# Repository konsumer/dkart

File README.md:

# dkart

An open-hardware and software Gameboy flash-cart and hardware peripheral framework that uses off-the-shelf hardware. The goal is to be ultra-cheap and simple.

## quickstart

If you just want to get started, go to [releases](https://github.com/konsumer/dkart/releases) and grab `dkart.gb`, and put it on a FAT32-formatted SDCard. Solder together the hardware, plug it in, and startup your gameboy.

## Hardware

It's meant to be very cheap & easy to put together. I made a PCB, and you can just solder in a [cheap ESP32 board](https://www.banggood.com/Geekcreit-ESP32-WiFibluetooth-Development-Board-Ultra-Low-Power-Consumption-Dual-Cores-Unsoldered-p-1214159.html) and the [SDCard shield](https://www.banggood.com/SD-Card-Module-Slot-Socket-Reader-Mp3-player-p-74105.html), and it should work.

Originally, I designed this as a custom circuit with really low-resource chips, but realized it was much easier and cheaper to just use more modern ready-made stuff.

Eventually I'd like to add an i2c bus that can be triggered/read from gameboy, so users can easily mess with hardware peripherals.

I am still working on the PCB & schematic. You can open hardware/Dkart.json at [easyeda](https://easyeda.com/).

### under consideration

Here are some other ideas I am looking at:

* [STM32F401](https://www.banggood.com/STM32F401-Development-Board-STM32F401CCU6-STM32F4-Learning-Board-p-1568897.html)
* [This board](https://www.banggood.com/LILYGO-TTGO-T2-ESP32-0_95-OLED-SD-Card-WiFi-bluetooth-Module-Development-Board-p-1270477.html) has a SDCard and OLED screen (and wifi/bluetooth)
* [cheap atmega2560 board](https://robotdyn.com/mega-2560-pro-mini-atmega2560-16au.html), works with arduino & has more IO/RAM/CPU, but still not big enough to hold every ROM
* [fast flash mem](https://www.sparkfun.com/products/15809) - I could load the rom & ram into flash temporarily on a lower-end microcontroller, then feed the data to the GB.
* [something like this](https://www.banggood.com/GY-Openlog-Cleanflight-Naze32-F3-Blackbox-Flash-Recorder-Module-p-1309673.html) has a lot of storage (32GB) but might not be fast enough
* [ready-made cart PCB](https://store.kitsch-bent.com/product/kk_gb_brkout) - with a little simple soldering and a big flash chip, I could probly get it all to fit inside a cartridge
* [something like this](http://ww1.microchip.com/downloads/en/DeviceDoc/20005023B.pdf) could be hooked up directly to GB pins, with maybe a little simple mode-management from a micro
* [sdfat](https://github.com/greiman/SdFat-beta) can do 3965.11 KB/Sec transfer in dedicated SPI with a slow cad, which should be fast enough
* [better SDCards](https://www.cameramemoryspeed.com/sd-memory-card-faq/fastest-memory-card/) can go much faster, so make sure to check SD speed (SDFst has a `bench` sketch)
* 3d print longer cart to hold more electronics if needed. [here](https://www.thingiverse.com/thing:2882206) are some nice variations. [Here](https://www.thingiverse.com/thing:3101147) is a nice modular design (opnscad - chnage logo, etc)
* I have a [ATxmega128A1 breakout](https://www.sparkfun.com/products/retired/9546) laying around, but it's discontinued at sparkfun. It has 78 IO and 32 MIPS! It only has 128kB of flash memory & 8 kB SRAM, but could be used easily with other things, possibly SD alone is fast enough.
* look at [this ESP32 cart](https://hackaday.io/project/20769-wifi-game-boy-cartridge). They have a lot of the same ideas.

## Firmware

The firmware runs on the device to emulate ROM/RAM reading/writing data to a microSD card formatted FAT16/FAT32/ExFat. The firmware is meant to be compiled in Arduino IDE. If you open serial-monitor when it's running, you'll see some debugging output. On Arch Linux, I had to use `arduino-PR-beta1.9-BUILD-117` for serial-monitor to work, due to some java error.

Files should all be in the root of the SDCard. The fRAM-size is 128K so you may hit limits if you have a ton of ROM files on the SD (limit should be around 8,737.) The file-list uses ROM-header-title, so if you have a bunch of the same ROM file-named differently, it will work, but in the ROM-list they will all have the same name. You can use this trick to have different copies of the same ROM with separate RAM files (like 1-per-song for nanoloop, for example.)

## Software

A menu runs on the Gameboy to choose the current ROM/RAM. When a ROM is chosen, the gameboy reboots using that ROM/RAM.

To compile, you need nodejs installed

```sh
cd software
npm i
npm run build
```

in the software directory. 

You can read more about it in [software](./software/README.md).

## TODO

* Actually Implement MBC1
* Get SD-loading working (on boot load into RAM from SD while playing logo)
* Get menu working (get list of ROMs from firmware, on menu selection, set mem, load on reboot & clear mem)
* Implement MBC5
* Replace Nintendo logo with mine
* add extra IO-functionality, reading/writing to a specific memory location to turn on "I/O mode" and be able to interface with other peripherals
* Add support for sub-directories
* Create a modern cross-platform GBDK-focused full dev-env (use wine & docker to run stuff like GBTD.) Alternately, write some web-based tools around GBDK.js to allow sprite/map/sound editing.

## License

* Hardware is licensed 
* Firmware & Software is licensed 

## Thanks

* Lots of hardware/firmware ideas from [here](https://dhole.github.io/post/gameboy_cartridge_emu_1/)
* Ideas for menu ROM programming from [gbdk_playground](https://github.com/mrombout/gbdk_playground), [gbdk-salvage](https://github.com/gbdk-salvage/grooves-game-boy-programming), & [GBSoundDemo](https://github.com/Zal0/GBSoundDemo)

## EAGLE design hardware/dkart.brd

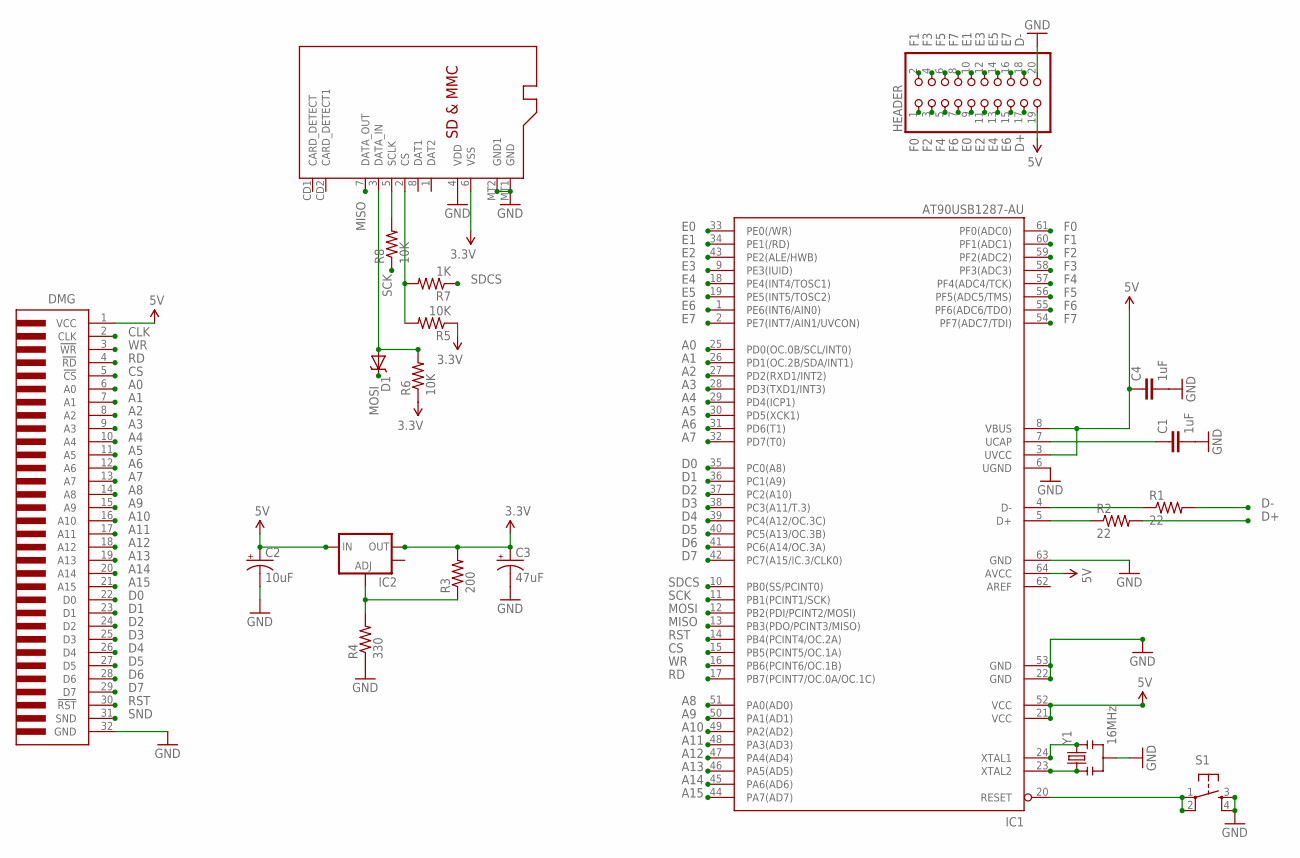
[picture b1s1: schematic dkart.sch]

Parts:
C1, C4: 1uF; 0805
C2: 10uF; EIA3528-KIT
C3: 47uF; EIA3528-KIT
D1: B340A; SMA-DIODE
DMG: GBCART-FULL; GBCART
HEADER: PINHD-2X10/90; 2X10/90
IC1: AT90USB1287-AU; TQFP64
IC2: V_REG_LM1117SOT223; SOT223
R1, R2: 22; 0805
R3: 200; 0805
R4: 330; 0805
R5, R6, R8: 10K; 0805
R7: 1K; 0805
S1: TAC_SWITCHSMD; TACTILE_SWITCH_SMD
SD: MICROSD
Y1: 16MHz; RESONATOR-SMD

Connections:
3.3V: C3.A (+), IC2.2 (OUT), R3.2, R5.1, R6.1, SD.6 (VSS)
5V: C2.A (+), C4.1, DMG.1 (VCC), HEADER.19, IC1.3 (UVCC), IC1.8 (VBUS), IC1.21 (VCC), IC1.52 (VCC), IC1.64 (AVCC), IC2.3 (IN)
A0: DMG.6 (A0), IC1.25 (PD0(OC.0B/SCL/INT0))
A1: DMG.7 (A1), IC1.26 (PD1(OC.2B/SDA/INT1))
A2: DMG.8 (A2), IC1.27 (PD2(RXD1/INT2))
A3: DMG.9 (A3), IC1.28 (PD3(TXD1/INT3))
A4: DMG.10 (A4), IC1.29 (PD4(ICP1))
A5: DMG.11 (A5), IC1.30 (PD5(XCK1))
A6: DMG.12 (A6), IC1.31 (PD6(T1))
A7: DMG.13 (A7), IC1.32 (PD7(T0))
A8: DMG.14 (A8), IC1.51 (PA0(AD0))
A9: DMG.15 (A9), IC1.50 (PA1(AD1))
A10: DMG.16 (A10), IC1.49 (PA2(AD2))
A11: DMG.17 (A11), IC1.48 (PA3(AD3))
A12: DMG.18 (A12), IC1.47 (PA4(AD4))
A13: DMG.19 (A13), IC1.46 (PA5(AD5))
A14: DMG.20 (A14), IC1.45 (PA6(AD6))
A15: DMG.21 (A15), IC1.44 (PA7(AD7))
CLK: DMG.2 (CLK)
CS: DMG.5 (!CS), IC1.15 (PB5(PCINT5/OC.1A))
D0: DMG.22 (D0), IC1.35 (PC0(A8))
D1: DMG.23 (D1), IC1.36 (PC1(A9))
D2: DMG.24 (D2), IC1.37 (PC2(A10))
D3: DMG.25 (D3), IC1.38 (PC3(A11/T.3))
D4: DMG.26 (D4), IC1.39 (PC4(A12/OC.3C))
D5: DMG.27 (D5), IC1.40 (PC5(A13/OC.3B))
D6: DMG.28 (D6), IC1.41 (PC6(A14/OC.3A))
D7: DMG.29 (D7), IC1.42 (PC7(A15/IC.3/CLK0))
D+: HEADER.17, R2.2
D-: HEADER.18, R1.2
E0: HEADER.9, IC1.33 (PE0(/WR))
E1: HEADER.10, IC1.34 (PE1(/RD))
E2: HEADER.11, IC1.43 (PE2(ALE/HWB))
E3: HEADER.12, IC1.9 (PE3(IUID))
E4: HEADER.13, IC1.18 (PE4(INT4/TOSC1))
E5: HEADER.14, IC1.19 (PE5(INT5/TOSC2))
E6: HEADER.15, IC1.1 (PE6(INT6/AIN0))
E7: HEADER.16, IC1.2 (PE7(INT7/AIN1/UVCON))
F0: HEADER.1, IC1.61 (PF0(ADC0))
F1: HEADER.2, IC1.60 (PF1(ADC1))
F2: HEADER.3, IC1.59 (PF2(ADC2))
F3: HEADER.4, IC1.58 (PF3(ADC3))
F4: HEADER.5, IC1.57 (PF4(ADC4/TCK))
F5: HEADER.6, IC1.56 (PF5(ADC5/TMS))
F6: HEADER.7, IC1.55 (PF6(ADC6/TDO))
F7: HEADER.8, IC1.54 (PF7(ADC7/TDI))
GND: C1.2, C2.C (-), C3.C (-), C4.2, DMG.32 (GND), HEADER.20, IC1.6 (UGND), IC1.22 (GND), IC1.53 (GND), IC1.63 (GND), R4.1, S1.3, S1.4, SD.4 (VDD), SD.MT1 (GND), SD.MT2 (GND1), Y1.2
MISO: IC1.13 (PB3(PDO/PCINT3/MISO)), SD.7 (DATA_OUT)
MOSI: D1.C, IC1.12 (PB2(PDI/PCINT2/MOSI))
unnamed: IC1.24 (XTAL1), Y1.3
unnamed: IC1.23 (XTAL2), Y1.1
unnamed: IC1.20 (RESET), S1.1, S1.2
unnamed: IC1.5 (D+), R2.1
unnamed: IC1.4 (D-), R1.1
unnamed: C1.1, IC1.7 (UCAP)
unnamed: IC2.1 (ADJ), R3.1, R4.2
unnamed: R8.2, SD.5 (SCLK)
unnamed: D1.A, R6.2, SD.3 (DATA_IN)
unnamed: R5.2, R7.2, SD.2 (CS)
RD: DMG.4 (!RD), IC1.17 (PB7(PCINT7/OC.0A/OC.1C))
RST: DMG.30 (!RST), IC1.14 (PB4(PCINT4/OC.2A))
SCK: IC1.11 (PB1(PCINT1/SCK)), R8.1
SDCS: IC1.10 (PB0(SS/PCINT0)), R7.1
SND: DMG.31 (SND)
WR: DMG.3 (!WR), IC1.16 (PB6(PCINT6/OC.1B))

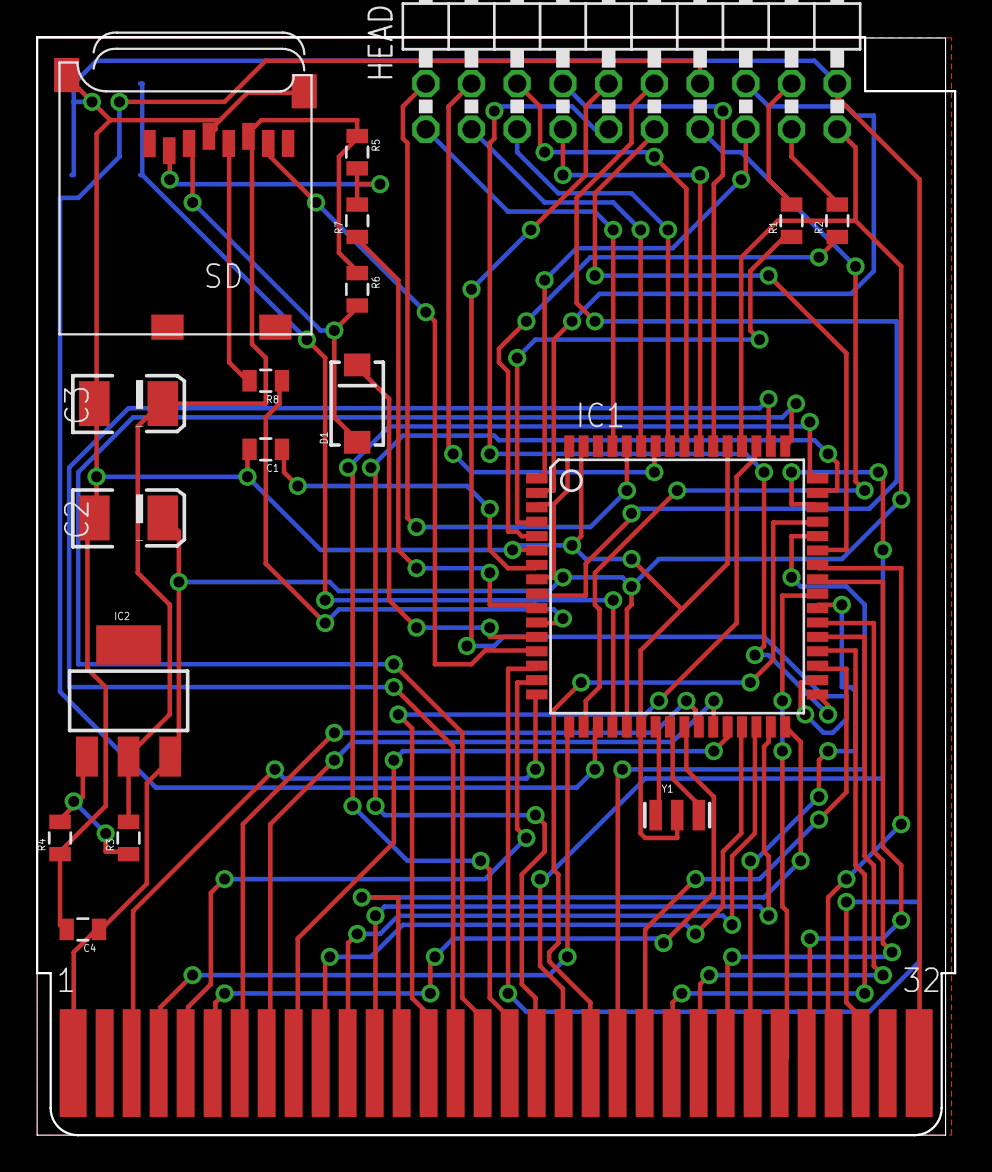
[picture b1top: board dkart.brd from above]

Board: 2 copper layers, 51.0 x 61.0 mm, 20 parts (1 on the bottom side), 63 nets.

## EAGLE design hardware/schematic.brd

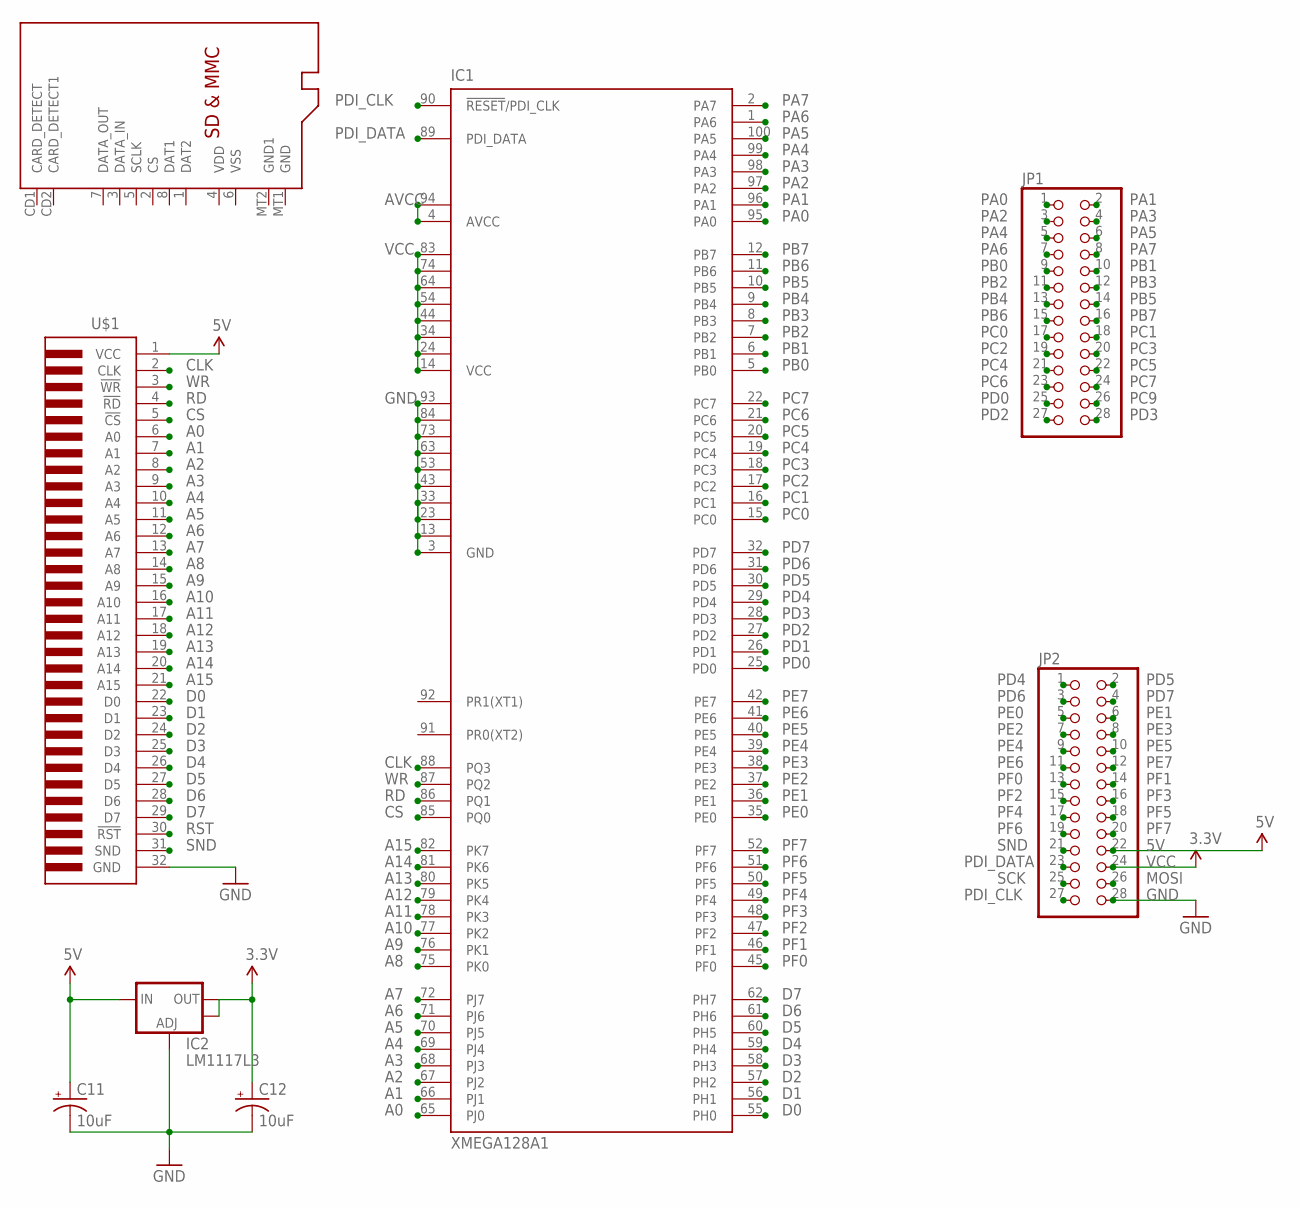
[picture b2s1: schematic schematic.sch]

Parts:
C11, C12: 10uF; EIA3216
IC1: XMEGA128A1; TQFP100
IC2: LM1117L3; SOT223
JP1, JP2: PINHD-2X14-CB; 2X14-CLEANBIG
U$1: GBCART-FULL; GBCART
U$5: MICROSD

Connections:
5V: C11.A (+), IC2.3 (IN), JP2.22, U$1.1 (VCC)
A0: IC1.65 (PJ0), U$1.6 (A0)
A1: IC1.66 (PJ1), U$1.7 (A1)
A2: IC1.67 (PJ2), U$1.8 (A2)
A3: IC1.68 (PJ3), U$1.9 (A3)
A4: IC1.69 (PJ4), U$1.10 (A4)
A5: IC1.70 (PJ5), U$1.11 (A5)
A6: IC1.71 (PJ6), U$1.12 (A6)
A7: IC1.72 (PJ7), U$1.13 (A7)
A8: IC1.75 (PK0), U$1.14 (A8)
A9: IC1.76 (PK1), U$1.15 (A9)
A10: IC1.77 (PK2), U$1.16 (A10)
A11: IC1.78 (PK3), U$1.17 (A11)
A12: IC1.79 (PK4), U$1.18 (A12)
A13: IC1.80 (PK5), U$1.19 (A13)
A14: IC1.81 (PK6), U$1.20 (A14)
A15: IC1.82 (PK7), U$1.21 (A15)
AVCC: IC1.4 (AVCC), IC1.94 (AVCC1)
CLK: IC1.88 (PQ3), U$1.2 (CLK)
CS: IC1.85 (PQ0), U$1.5 (!CS)
D0: IC1.55 (PH0), U$1.22 (D0)
D1: IC1.56 (PH1), U$1.23 (D1)
D2: IC1.57 (PH2), U$1.24 (D2)
D3: IC1.58 (PH3), U$1.25 (D3)
D4: IC1.59 (PH4), U$1.26 (D4)
D5: IC1.60 (PH5), U$1.27 (D5)
D6: IC1.61 (PH6), U$1.28 (D6)
D7: IC1.62 (PH7), U$1.29 (D7)
GND: C11.C (-), C12.C (-), IC1.3 (GND), IC1.13 (GND1), IC1.23 (GND2), IC1.33 (GND3), IC1.43 (GND4), IC1.53 (GND5), IC1.63 (GND6), IC1.73 (GND7), IC1.84 (GND8), IC1.93 (GND9), IC2.1 (ADJ), JP2.28, U$1.32 (GND)
MOSI: JP2.26
PA0: IC1.95 (PA0), JP1.1
PA1: IC1.96 (PA1), JP1.2
PA2: IC1.97 (PA2), JP1.3
PA3: IC1.98 (PA3), JP1.4
PA4: IC1.99 (PA4), JP1.5
PA5: IC1.100 (PA5), JP1.6
PA6: IC1.1 (PA6), JP1.7
PA7: IC1.2 (PA7), JP1.8
PB0: IC1.5 (PB0), JP1.9
PB1: IC1.6 (PB1), JP1.10
PB2: IC1.7 (PB2), JP1.11
PB3: IC1.8 (PB3), JP1.12
PB4: IC1.9 (PB4), JP1.13
PB5: IC1.10 (PB5), JP1.14
PB6: IC1.11 (PB6), JP1.15
PB7: IC1.12 (PB7), JP1.16
PC0: IC1.15 (PC0), JP1.17
PC1: IC1.16 (PC1), JP1.18
PC2: IC1.17 (PC2), JP1.19
PC3: IC1.18 (PC3), JP1.20
PC4: IC1.19 (PC4), JP1.21
PC5: IC1.20 (PC5), JP1.22
PC6: IC1.21 (PC6), JP1.23
PC7: IC1.22 (PC7), JP1.24
PC9: JP1.26
PD0: IC1.25 (PD0), JP1.25
PD1: IC1.26 (PD1)
PD2: IC1.27 (PD2), JP1.27
PD3: IC1.28 (PD3), JP1.28
PD4: IC1.29 (PD4), JP2.1
PD5: IC1.30 (PD5), JP2.2
PD6: IC1.31 (PD6), JP2.3
PD7: IC1.32 (PD7), JP2.4
PDI_CLK: IC1.90 (!RESET!/PDI_CLK), JP2.27
PDI_DATA: IC1.89 (PDI_DATA), JP2.23
PE0: IC1.35 (PE0), JP2.5
PE1: IC1.36 (PE1), JP2.6
PE2: IC1.37 (PE2), JP2.7
PE3: IC1.38 (PE3), JP2.8
PE4: IC1.39 (PE4), JP2.9
PE5: IC1.40 (PE5), JP2.10
PE6: IC1.41 (PE6), JP2.11
PE7: IC1.42 (PE7), JP2.12
PF0: IC1.45 (PF0), JP2.13
PF1: IC1.46 (PF1), JP2.14
PF2: IC1.47 (PF2), JP2.15
PF3: IC1.48 (PF3), JP2.16
PF4: IC1.49 (PF4), JP2.17
PF5: IC1.50 (PF5), JP2.18
PF6: IC1.51 (PF6), JP2.19
PF7: IC1.52 (PF7), JP2.20
RD: IC1.86 (PQ1), U$1.4 (!RD)
RST: U$1.30 (!RST)
SCK: JP2.25
SND: JP2.21, U$1.31 (SND)
VCC: C12.A (+), IC1.14 (VCC), IC1.24 (VCC1), IC1.34 (VCC2), IC1.44 (VCC3), IC1.54 (VCC4), IC1.64 (VCC5), IC1.74 (VCC6), IC1.83 (VCC7), IC2.2 (OUT), IC2.4 (OUT), JP2.24
WR: IC1.87 (PQ2), U$1.3 (!WR)

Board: 2 copper layers, 8 parts (0 on the bottom side), 82 nets, no tracks yet.

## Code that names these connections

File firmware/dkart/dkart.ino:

///////////////
//  WARNING  //
///////////////
// this isn't done, yet.

#include <SD.h>

// contains PROGMEM for dkart in rom[]
// eventually, this might be on the SD
// maybe not, to remove need for SDtoSROM() bootstrap time
#include "dkart.h"

/*

Hardware Connections:

Teensy 2++

for i2c EEPROM:
SCL   - PD0
SDA   - PD1
address pins 1&2 on EEPROM tied to GND

for interrupts:
WR     - PE6 (arduino 18)
CS     - PE7 (arduino 19)

for SDCard
SS     - PB0 (arduino 20)
SCLK   - PB1 (arduino 21)
MOSI   - PB2 (arduino 22)
MISO   - PB3 (arduino 23)

Gameboy Data/Address
D0-D7  - PF0-PF7 (arduino 38-45)
A0-A7  - PA0-PA7 (inside pins: arduino 28-35)
A8-A15 - PC0-PC7 (arduino 10-17)

*/

File dataFile;

// read WR & CS when either of them change.
// also read address lines & read/write data lines
void intReadWriteCS(){
  word address = word(PINC, PINA);
  
  // Data read/write based on status of WR (active-low)
  if (digitalRead(18)){ // WR HIGH
    DDRF = 0xFF; // Data: OUTPUT
    // TODO: use CS pin to choose bank
    // TODO: this is dkart only, for now
    if (address < 12080){
      PORTF = (char)pgm_read_word(&(rom[address]));
    }else{
      PORTF = 0xFF;
    }
  }else{
    DDRF = 0x00; // Data: INPUT
  }
}

// read SD copy of ROM to SROM
void SDtoSROM(char* rom){
  dataFile = SD.open(rom);
  if (dataFile) {
    while (dataFile.available()) {
      
    }
  }
  dataFile.close();
  // TODO: check for game RAM file, write it to SROM, too
}

void setup(){
  // Address: INPUT
  DDRA = 0x00;
  DDRC = 0x00;
  
  // Data: OUTPUT
  DDRF = 0xFF;
  
  // TODO:
  // check if current ROM is loaded in SROM
  // if no, load it from SD
  // if yes, serve it instead of dkart
  
  // read SD of current-ROM to SROM
  // normally, this would be called on game ROM select, and merely checked in setup() for dkart service
  SDtoSROM("mario.gb");
  
  // read WR & CS when either of them change.
  // also read address lines & read/write data lines
  pinMode(18, INPUT);
  pinMode(19, INPUT);
  attachInterrupt(6, intReadWriteCS, CHANGE);
  attachInterrupt(7, intReadWriteCS, CHANGE);
}

void loop(){
}

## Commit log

2013-01-22 removed extra eagle files
2013-01-22 moved docs out of repo
2013-01-23 improved menu to demo basic flow
2013-01-23 added licenses
2013-01-23 mis-spelled license
2013-01-23 added links and credits
2013-01-23 need to test last page for menu system, start of that
2013-01-23 better to leave off email for Christopher
2013-01-23 added instructions on demo software
2013-01-23 better page-bar
2013-01-23 added license for future firmware
2013-01-23 like non-inverted indicator better
2013-01-24 more playing with menu
2013-01-24 starting over with new hardware ideas
2013-01-24 added experiment cart
2013-01-24 mend
2013-01-24 I like this menu better.
2013-01-28 minor editing
2013-02-12 working on using at90usb1287
2013-02-12 docs reflect new direction
2013-02-12 minor docs edit
2013-02-12 moved USB to header
2013-02-12 minor doc chages
2013-02-12 board design complete, improved schematic, ready for hardware testing
2013-02-12 beginning of firmware. untested
2013-02-12 minor changes
2013-05-20 added makefile for firmware
2013-05-20 added serial_log for quick logging of serial output
2013-05-20 ignore DStore
2013-05-20 improved hardware design
2013-05-20 starting work on new ideas
2020-03-04 move to STM32F401
2020-03-04 note about old design
2020-03-04 info about deps
2020-03-04 thank learning resources
2020-03-04 clearer other OS language
2020-03-04 working on ideas around ROM menu
2020-03-04 no arduino
2020-03-04 link sd shield
2020-03-05 working on improving menu
2020-03-06 improved menu
2020-03-06 notes on hardware improvements
2020-03-06 notes about 3d printing
2020-03-06 more like it will be later
2020-03-06 minor efficeincy tweaks
2020-03-06 more minor efficeincy tweaks
2020-03-07 typo
2020-03-07 allow tag&release
2020-03-07 playing with RAM ideas
2020-03-07 tag not working
2020-03-07 backing out of release and SRAM ideas
2020-03-08 starting to work on ideas for command and ROM management
2020-03-08 better memory sharing with cart, but bad type math on page up/down
2020-03-08 use tile-font to fix gbdk bugs and fit more on screen
2020-03-08 use local vars to track menu, for better perf
2020-03-08 regular build
2020-03-08 fixed offset for choice display
2020-03-08 comment menu functions
2020-03-08 better const naming
2020-03-08 handle short pages
2020-03-08 remove mock
2020-03-08 use LEN_PAGE for status at bottom
2020-03-08 better order for mem/tiles
2020-03-09 starting on firmware
2020-03-09 use yay on arch
2020-03-09 use subtract for rom-page to get order right
2020-03-09 firmware ideas
2020-03-09 better hardware parts
2020-03-09 start of PCB
2020-03-10 new ideas for firmware
2020-03-10 try to get name form ROM header
2020-03-10 starting work on new SRAM idea - broken for now
2020-03-10 working on new ideas with SAV
2020-03-10 I think firmware bytes for count were reversed
2020-03-10 RAM size is 32768
2020-03-10 I think I need to seek in firmware SAV 0-fill
2020-03-11 working on fixing menu
2020-03-11 enable splash, disablecount for now
2020-03-11 I think menu ROM is functional
2020-03-11 async LED blinker for errors in firmware
2020-03-13 non-working ideas for in-emulator debug
2020-04-22 better splash
2020-05-08 add nintendo replacement logo
2020-05-08 hardware notes
2020-05-08 start of node-based build tools
2020-05-20 Create LICENSE

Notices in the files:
parts and their libraries:
SparkFun-PowerIC: Licensing: CC v3.0 Share-Alike You are welcome to use this library for commercial purposes.
